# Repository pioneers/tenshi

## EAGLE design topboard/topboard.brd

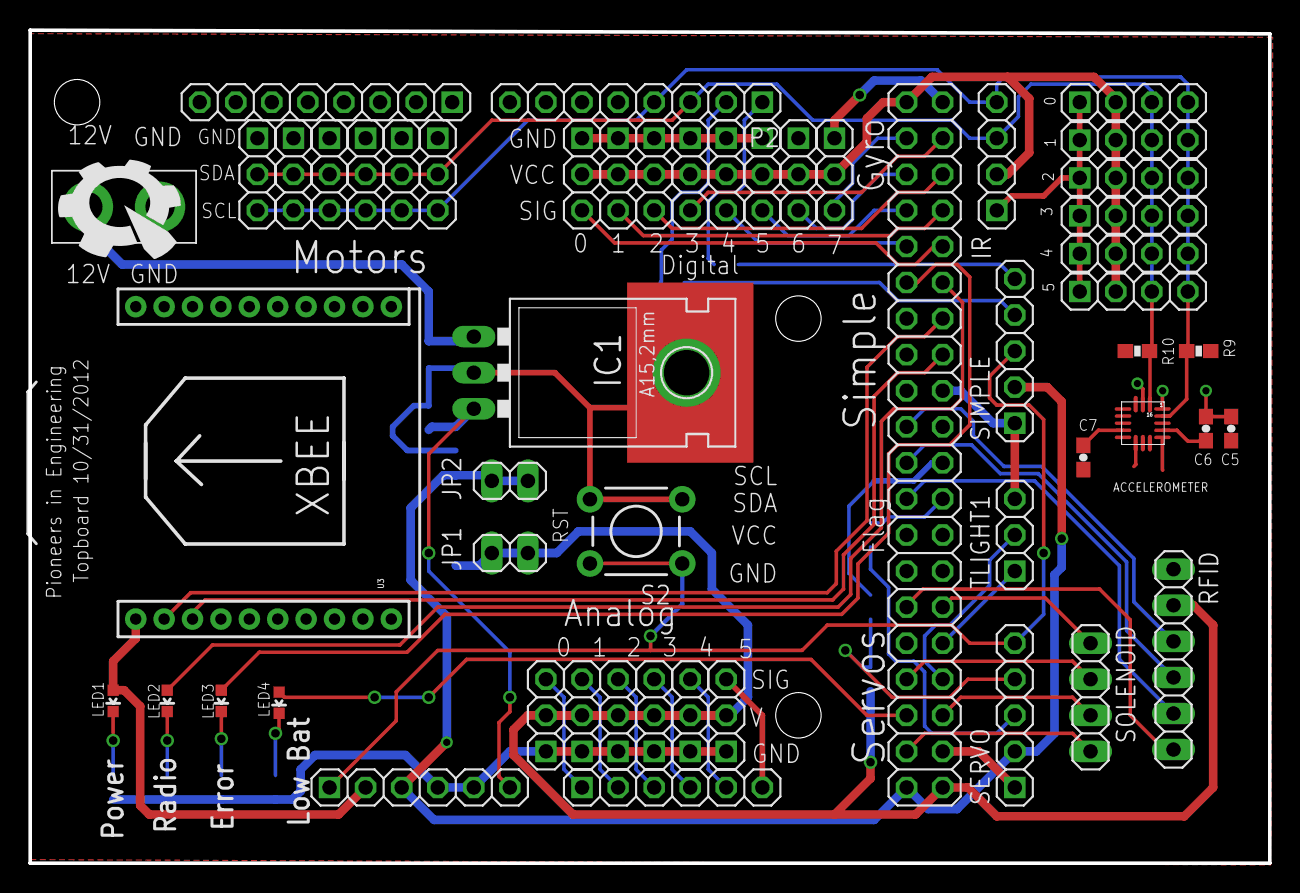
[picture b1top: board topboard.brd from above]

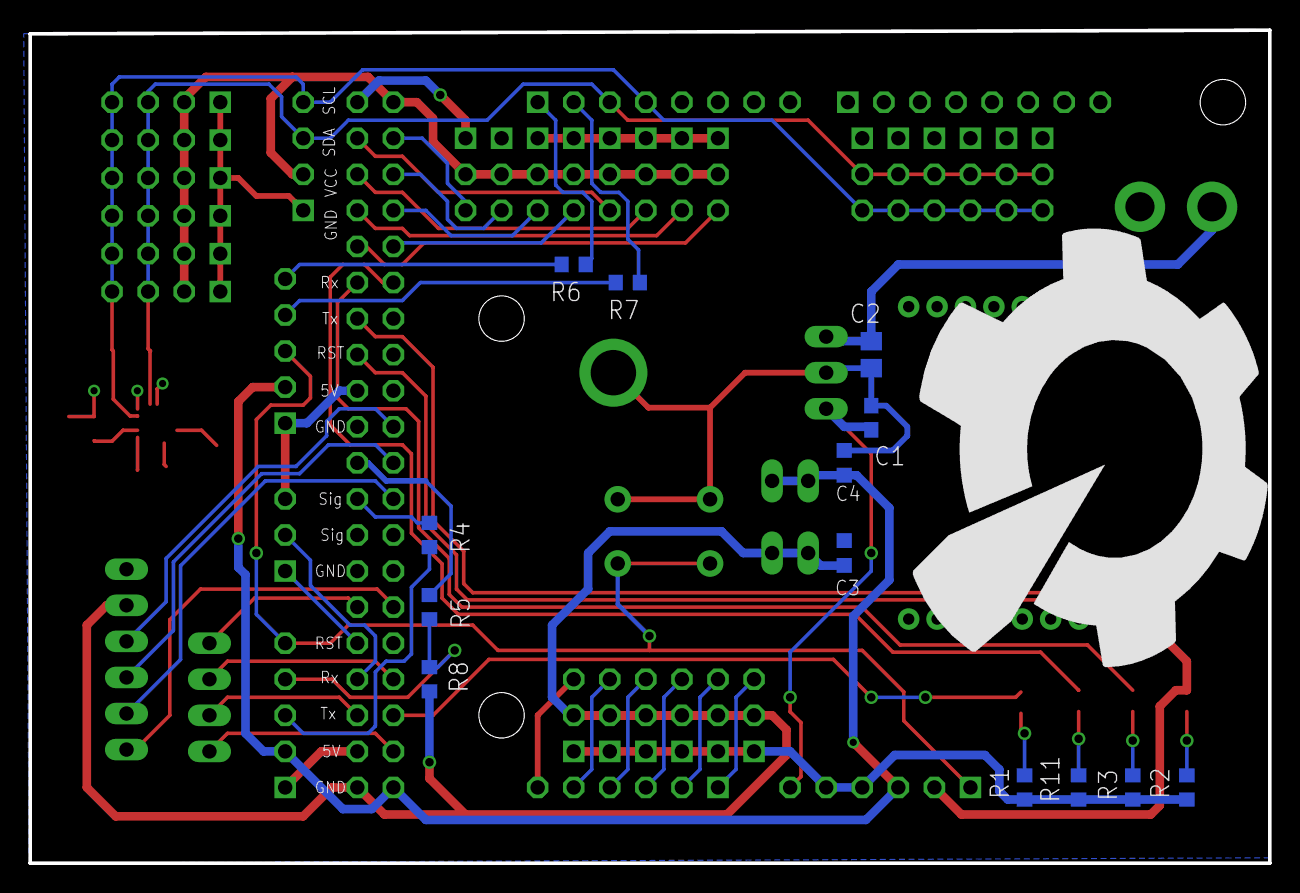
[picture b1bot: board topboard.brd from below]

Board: 2 copper layers, 87.3 x 58.7 mm, 68 parts (14 on the bottom side), 51 nets.

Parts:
0, 1, 2, 3, 4, 5: 1X04-S
A0, A1, A2, A3, A4, A5: 1X03-S
ACCELEROMETER: MMA8451QT
C1: .1uF; C0603
C2: 10uF; C0805
C3, C4: .1uF; C0603K
C5, C6: 0.1u; 0603-CAP
C7: 4.7u; 0603-CAP
D51, D52, D53, D54, D55, D56, D57, D58: 1X03-S
IC1: 78XXL
IR: 1X04-S
JP1: 3.3V; 1X02
JP2: 5v; 1X02
JP3: 1X02_XTRA_BIG
LED1, LED2, LED3, LED4: LED-0603
M1, M2, M3, M4, M5, M6: 1X03-S
P1, P2: 1X08-S
P3: 2X20
P4, P5: 1X06-S
R1, R2, R3, R7, R11: R0603
R4, R5, R6: 200; R0603
R8: 220K; R0603
R9, R10: 4.7k; 0603-RES
RFID: 1X06
S2: TACTILE-PTH
SERVO: 1X05-S
SIMPLE: Simple; 1X05-S
SOLENOID: 1X04
TLIGHT1: 1X03-S
U3: XBEE-1B2; XBEE-SILK
U$2: PIE-LOGO
U$3: PIE-LOGO-SMALL

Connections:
12V: C2.1, IC1.IN, JP3.2
+5V: C4.1, JP2.1, JP2.2, P3.39, P5.3, SERVO.2, SIMPLE.2
ADC0/IO28*: A0.3, P4.1
ADC1/IO26*: A1.3, P4.2
ADC2/IO24*: A2.3, P4.3
ADC3/AOUT/IO22*: A3.3, P4.4
ADC4/IO29: A4.3, P4.5
ADC5/IO32: A5.3, P4.6
GND: 0.1, 1.1, 2.1, 3.1, 4.1, 5.1, A0.1, A1.1, A2.1, A3.1, A4.1, A5.1, ACCELEROMETER.5, ACCELEROMETER.7, C1.2, C2.2, C3.2, C4.2, C5.2, C6.2, D51.1, D52.1, D53.1, D54.1, D55.1, D56.1, D57.1, D58.1, IC1.GND, IC1.P$1, IC1.P$2, IR.1, JP3.1, M1.1, M2.1, M3.1, M4.1, M5.1, M6.1, P1.7, P3.2, P3.18, P3.38, P5.4, P5.5, R1.1, R2.1, R3.1, R11.1, RFID.1, S2.3, S2.4, SERVO.1, SIMPLE.1, TLIGHT1.3, U3.10
IO3/RXD1: P3.22, R5.1
IO5/TXD1: P3.24, R4.1
IO6/MOSI1: P3.23, RFID.5
IO8/MISO1: P3.21, RFID.4
IO10/SCK1: P3.19, RFID.3
IO13/TXD3: P3.16, U3.3
IO17/RXD3: P3.14, U3.2
IO51: D51.3, P3.4
IO52: D52.3, P3.3
IO53: D53.3, P3.6
IO54: D54.3, P3.5
IO55: D55.3, P3.8
IO56: D56.3, P3.7
IO57: D57.3, P3.10
IO58: D58.3, P3.9
IO59: LED2.A, P3.12
IO60: LED3.A, P3.11
IO61: P3.36, SOLENOID.3
IO62: LED4.A, P3.35
IO63: P3.34, TLIGHT1.2
IO64: P3.33, SOLENOID.2
IO65: P3.32, TLIGHT1.1
IO66: P3.30, SOLENOID.1
IO67: P3.29, RFID.6
IO68: P3.37, SOLENOID.4
unnamed: LED4.C, R1.2
unnamed: LED1.C, R2.2
unnamed: LED2.C, R3.2
unnamed: R6.2, SIMPLE.5
unnamed: R4.2, SERVO.3
unnamed: R7.2, SIMPLE.4
unnamed: R5.2, R8.2, SERVO.4
unnamed: LED3.C, R11.2
unnamed: ACCELEROMETER.12, C7.2
unnamed: ACCELEROMETER.2, C6.1
RESET#: P5.1, S2.1, S2.2, SERVO.5, SIMPLE.3
RXD0/IO20*: P2.1, R6.1
SCL0/IO31*: 0.4, 1.4, 2.4, 3.4, 4.4, 5.4, ACCELEROMETER.4, IR.4, M1.3, M2.3, M3.3, M4.3, M5.3, M6.3, P2.4, R9.1
SDA0/IO33*: 0.3, 1.3, 2.3, 3.3, 4.3, 5.3, ACCELEROMETER.6, IR.3, M1.2, M2.2, M3.2, M4.2, M5.2, M6.2, P2.3, R10.1
TXD0/IO18*: P2.2, R7.1
VCC: 0.2, 1.2, 2.2, 3.2, 4.2, 5.2, A0.2, A1.2, A2.2, A3.2, A4.2, A5.2, ACCELEROMETER.1, ACCELEROMETER.14, C3.1, C5.1, C7.1, D51.2, D52.2, D53.2, D54.2, D55.2, D56.2, D57.2, D58.2, IR.2, JP1.1, JP1.2, LED1.A, P3.1, P3.40, P5.2, R8.1, R9.2, R10.2, RFID.2, U3.1
VIN: C1.1, IC1.OUT, P5.6

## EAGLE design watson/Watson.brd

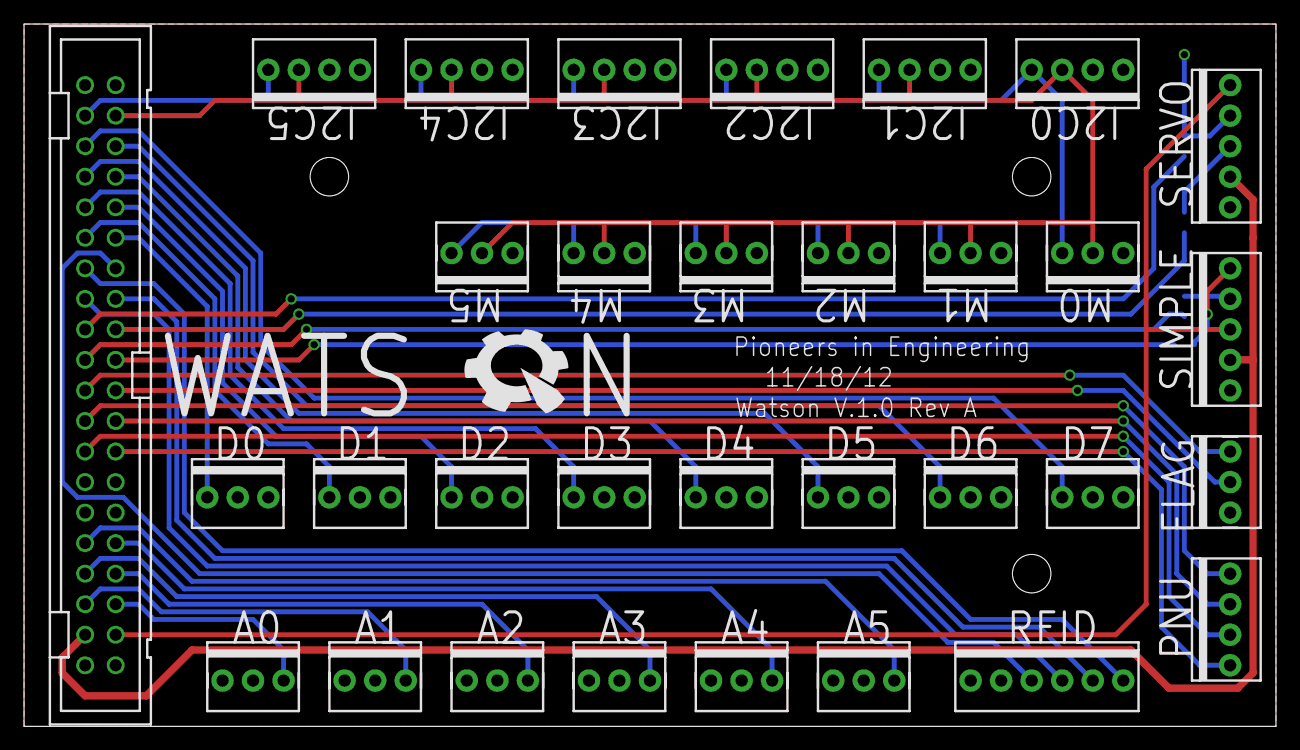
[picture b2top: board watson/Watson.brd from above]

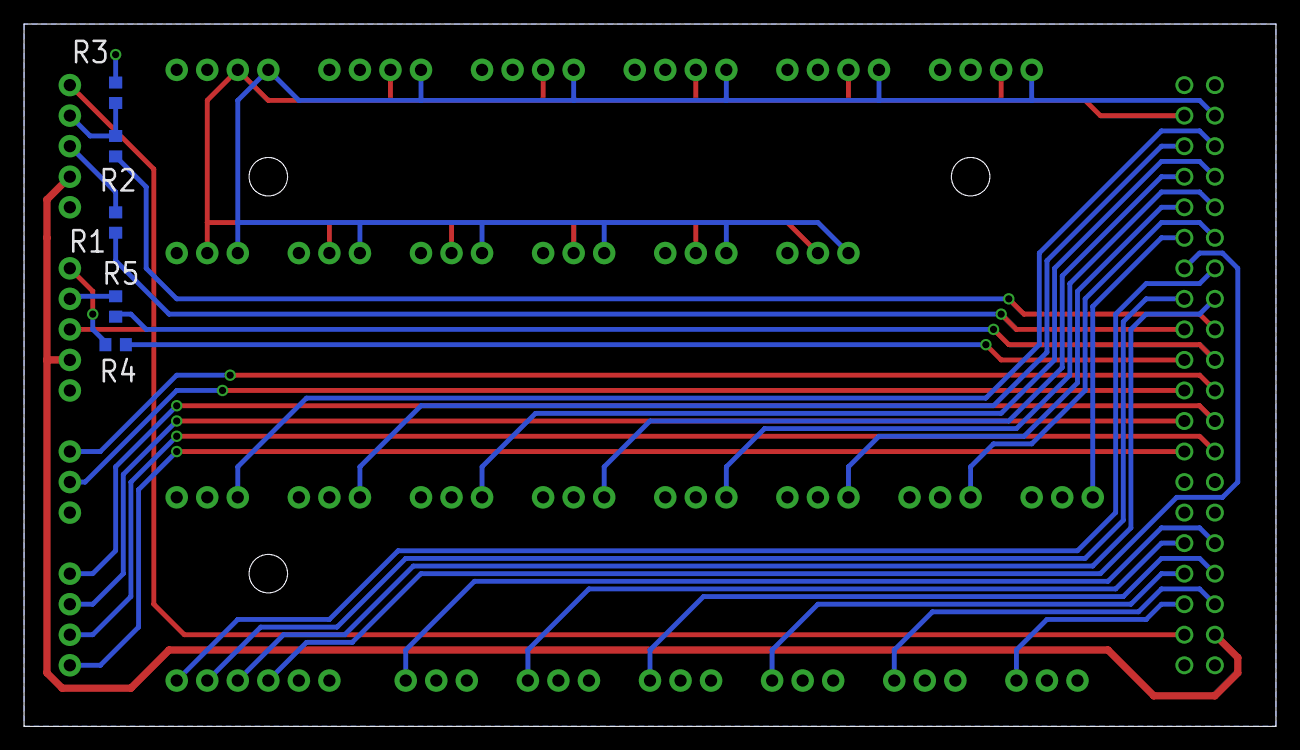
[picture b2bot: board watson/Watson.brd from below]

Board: 2 copper layers, 104.1 x 58.4 mm, 38 parts (5 on the bottom side), 38 nets.

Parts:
A0, A1, A2, A3, A4, A5: 1X03
D0, D1, D2, D3, D4, D5, D6, D7: 1X03
FLAG: 1X03
I2C0, I2C1, I2C2, I2C3, I2C4, I2C5: M04; 1X04
M0, M1, M2, M3, M4, M5: 1X03
PNU: M04; 1X04
R1, R2, R4, R5: 200; R0603
R3: 200k; R0603
RFID: M06; 1X06
SERVO: Servos; 1X05
SIMPLE: Servos; 1X05
U$1: WATSON
X1: 2540-FLAT; PAK100/2500-40

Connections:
5V: SERVO.2, SIMPLE.2, X1.4
ADC0: A5.3, X1.10
ADC1: A4.3, X1.9
ADC2: A3.3, X1.8
ADC3: A2.3, X1.7
ADC4: A1.3, X1.6
ADC5: A0.3, X1.5
GND: A0.1, A1.1, A2.1, A3.1, A4.1, A5.1, D0.3, D1.3, D2.3, D3.3, D4.3, D5.3, D6.3, D7.3, FLAG.1, I2C0.1, I2C1.1, I2C2.1, I2C3.1, I2C4.1, I2C5.1, M0.1, M1.1, M2.1, M3.1, M4.1, M5.1, RFID.1, SERVO.1, SIMPLE.1, X1.1, X1.39
IO21: PNU.3, X1.17
IO51: D7.1, X1.36
IO52: D6.1, X1.35
IO53: D5.1, X1.34
IO54: D4.1, X1.33
IO55: D3.1, X1.32
IO56: D2.1, X1.31
IO57: D1.1, X1.30
IO58: D0.1, X1.29
IO63: PNU.2, X1.16
IO64: PNU.1, X1.15
IO65: PNU.4, X1.18
IO66: FLAG.3, X1.20
IO67: FLAG.2, X1.19
IO/SELECT: RFID.6, X1.28
MISO: RFID.4, X1.26
MOSI: RFID.5, X1.25
unnamed: R2.1, R3.1, SERVO.4
unnamed: R1.1, SERVO.3
unnamed: R4.1, SIMPLE.5
unnamed: R5.1, SIMPLE.4
RESET#: SERVO.5, SIMPLE.3, X1.3
RXD1: R2.2, X1.24
RXD2: R5.2, X1.22
SCK: RFID.3, X1.27
SCL: I2C0.4, I2C1.4, I2C2.4, I2C3.4, I2C4.4, I2C5.4, M0.3, M1.3, M2.3, M3.3, M4.3, M5.3, X1.38
SDA: I2C0.3, I2C1.3, I2C2.3, I2C3.3, I2C4.3, I2C5.3, M0.2, M1.2, M2.2, M3.2, M4.2, M5.2, X1.37
TXD1: R1.2, X1.23
TXD2: R4.2, X1.21
VCC: A0.2, A1.2, A2.2, A3.2, A4.2, A5.2, D0.2, D1.2, D2.2, D3.2, D4.2, D5.2, D6.2, D7.2, I2C0.2, I2C1.2, I2C2.2, I2C3.2, I2C4.2, I2C5.2, R3.2, RFID.2, X1.2, X1.40

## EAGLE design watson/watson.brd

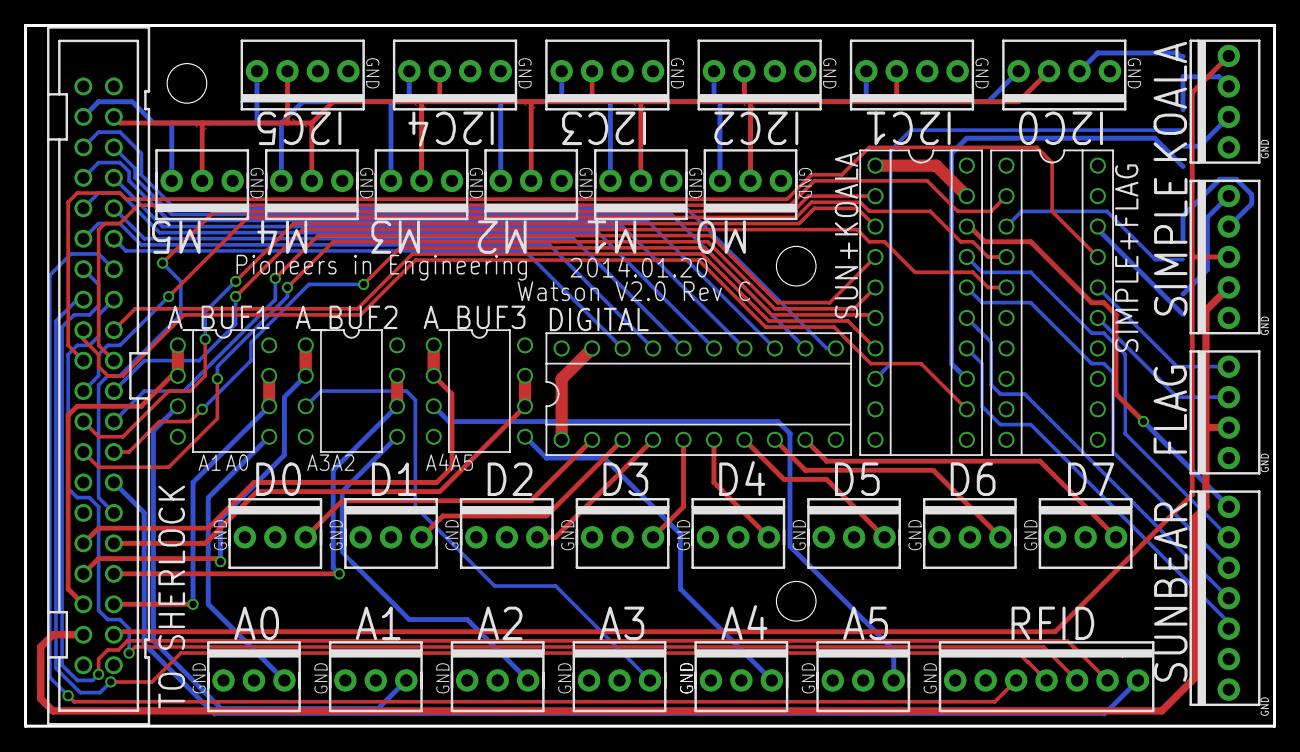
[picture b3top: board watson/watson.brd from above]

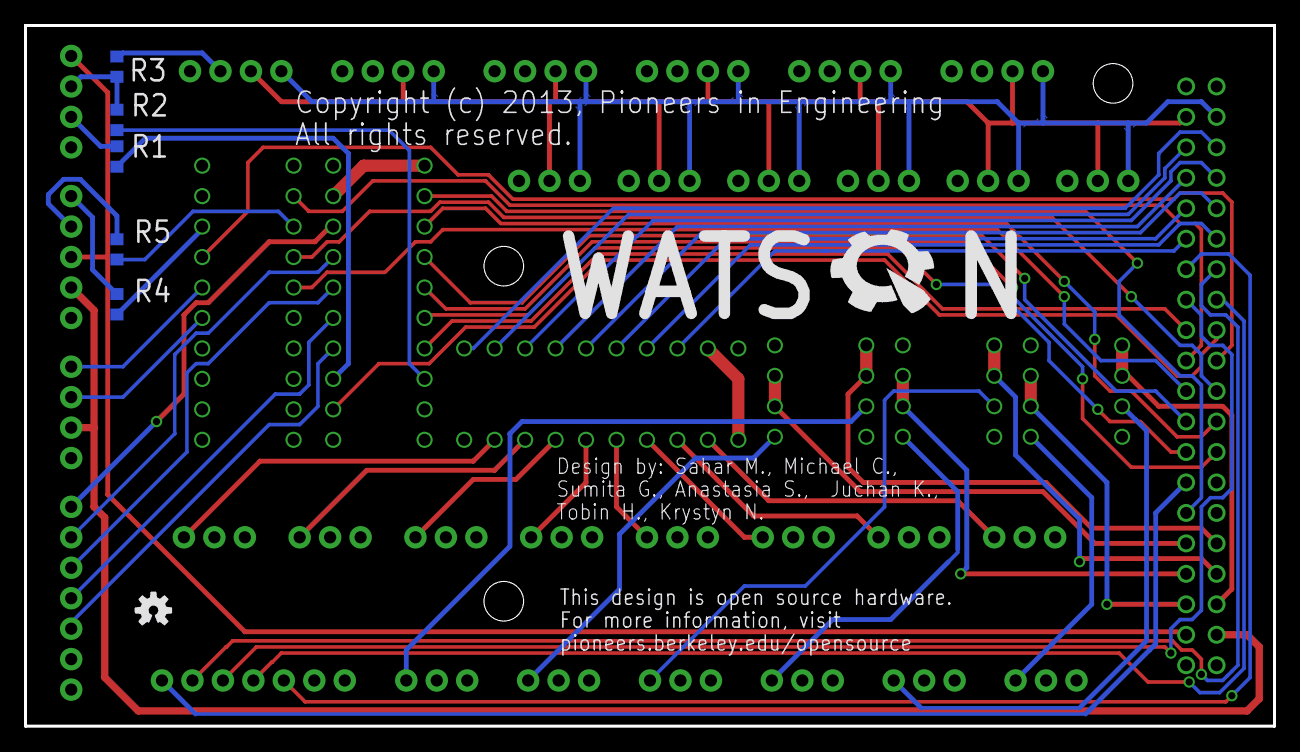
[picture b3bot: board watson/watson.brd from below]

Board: 2 copper layers, 104.1 x 58.4 mm, 48 parts (7 on the bottom side), 65 nets.

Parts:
A0, A1, A2, A3, A4, A5: 1X03-MTA
A_BUF1, A_BUF2, A_BUF3: OPAMP_DUAL_DIL
D0, D1, D2, D3, D4, D5, D6, D7: 1X03-MTA
DIGITAL: DIGITAL_BUFFER_SOCKET
FLAG: 1X04-MTA
I2C0, I2C1, I2C2, I2C3, I2C4, I2C5: 1X04-MTA
KOALA: Servos; 1X04-MTA
M0, M1, M2, M3, M4, M5: 1X03-MTA
R1, R2, R4, R5: 200; R0603
R3: 200k; R0603
RFID: M07; 1X07-MTA
SHERLOCK: 2540-; PAK100/2500-40
SIMPLE: Servos; 1X05-MTA
SIMPLE+FLAG: DIGITAL_BUFFER_SOCKET
SUN+KOALA: DIGITAL_BUFFER_SOCKET
SUNBEAR: M07; 1X07-MTA
U$1: WATSON
U$4: Mounting + Test; STAND-OFF
U$5: Test; STAND-OFF
U$6: OSHW-LOGO-S
U$7: Mounting; STAND-OFF

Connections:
+5V: FLAG.2, SHERLOCK.4, SIMPLE.2
A0: A0.3, A_BUF1.5
A1: A1.3, A_BUF1.3
A2: A2.3, A_BUF2.5
A3: A3.3, A_BUF2.3
A4: A4.3, A_BUF3.5
A5: A5.3, A_BUF3.3
ADC0/IO28*: A_BUF3.1, A_BUF3.2, SHERLOCK.10
ADC1/IO26*: A_BUF3.6, A_BUF3.7, SHERLOCK.9
ADC2/IO24*: A_BUF2.1, A_BUF2.2, SHERLOCK.8
ADC3/AOUT/IO22*: A_BUF2.6, A_BUF2.7, SHERLOCK.7
ADC4/IO29: A_BUF1.1, A_BUF1.2, SHERLOCK.6
ADC5/IO32: A_BUF1.6, A_BUF1.7, SHERLOCK.5
D0/IO58: D0.3, DIGITAL.A1
D1/IO57: D1.3, DIGITAL.A2
D2/IO56: D2.3, DIGITAL.A3
D3/IO55: D3.3, DIGITAL.A4
D4/IO54: D4.3, DIGITAL.A5
D5/IO53: D5.3, DIGITAL.A6
D6/IO52: D6.3, DIGITAL.A7
D7/IO51: D7.3, DIGITAL.A8
GND: A0.1, A1.1, A2.1, A3.1, A4.1, A5.1, A_BUF1.4, A_BUF2.4, A_BUF3.4, D0.1, D1.1, D2.1, D3.1, D4.1, D5.1, D6.1, D7.1, DIGITAL.G1, DIGITAL.G2, DIGITAL.GND, FLAG.1, I2C0.1, I2C1.1, I2C2.1, I2C3.1, I2C4.1, I2C5.1, KOALA.1, M0.1, M1.1, M2.1, M3.1, M4.1, M5.1, RFID.1, SHERLOCK.1, SHERLOCK.39, SIMPLE.1, SIMPLE+FLAG.G1, SIMPLE+FLAG.G2, SIMPLE+FLAG.GND, SUN+KOALA.G1, SUN+KOALA.G2, SUN+KOALA.GND, SUNBEAR.1
IO3/RXD1: SHERLOCK.24, SUN+KOALA.Y7
IO5/TXD1: SHERLOCK.23, SUN+KOALA.A6
IO6/MOSI1: RFID.5, SHERLOCK.25
IO8/MISO1: RFID.4, SHERLOCK.26
IO10/SCK1: RFID.3, SHERLOCK.27
IO11/RTS1: RFID.7, SHERLOCK.13
IO12: RFID.6, SHERLOCK.28
IO21: SHERLOCK.17, SUN+KOALA.A3
IO38/RXD2: SHERLOCK.22, SIMPLE+FLAG.Y2
IO39/TXD2: SHERLOCK.21, SIMPLE+FLAG.A1
IO51: DIGITAL.Y8, SHERLOCK.36
IO52: DIGITAL.Y7, SHERLOCK.35
IO53: DIGITAL.Y6, SHERLOCK.34
IO54: DIGITAL.Y5, SHERLOCK.33
IO55: DIGITAL.Y4, SHERLOCK.32
IO56: DIGITAL.Y3, SHERLOCK.31
IO57: DIGITAL.Y2, SHERLOCK.30
IO58: DIGITAL.Y1, SHERLOCK.29
IO61: SHERLOCK.11, SUN+KOALA.A1
IO63: SHERLOCK.16, SUN+KOALA.A4
IO64: SHERLOCK.15, SUN+KOALA.A5
IO65: SHERLOCK.18, SUN+KOALA.A2
IO66: SHERLOCK.20, SIMPLE+FLAG.A3
IO67: SHERLOCK.19, SIMPLE+FLAG.A4
K1/IO5/TXD1: R1.2, SUN+KOALA.Y6
K2/IO3/RXD1: R2.2, SUN+KOALA.A7
unnamed: KOALA.3, R2.1, R3.1
unnamed: KOALA.2, R1.1
unnamed: R4.1, SIMPLE.5
unnamed: R5.1, SIMPLE.4
RESET#: KOALA.4, SHERLOCK.3, SIMPLE.3
SB1/IO61: SUN+KOALA.Y1, SUNBEAR.7
SB2/IO65: SUN+KOALA.Y2, SUNBEAR.6
SB3/IO21: SUN+KOALA.Y3, SUNBEAR.5
SB4/IO63: SUN+KOALA.Y4, SUNBEAR.4
SB5/IO64: SUN+KOALA.Y5, SUNBEAR.3
SCL0/IO31*: I2C0.4, I2C1.4, I2C2.4, I2C3.4, I2C4.4, I2C5.4, M0.3, M1.3, M2.3, M3.3, M4.3, M5.3, SHERLOCK.38
SDA0/IO33*: I2C0.3, I2C1.3, I2C2.3, I2C3.3, I2C4.3, I2C5.3, M0.2, M1.2, M2.2, M3.2, M4.2, M5.2, SHERLOCK.37
SIM/IO38/RXD2: R5.2, SIMPLE+FLAG.A2
SIM/IO39/TXD2: R4.2, SIMPLE+FLAG.Y1
TF1/IO66: FLAG.4, SIMPLE+FLAG.Y3
TF2/IO67: FLAG.3, SIMPLE+FLAG.Y4
VCC: A0.2, A1.2, A2.2, A3.2, A4.2, A5.2, A_BUF1.8, A_BUF2.8, A_BUF3.8, D0.2, D1.2, D2.2, D3.2, D4.2, D5.2, D6.2, D7.2, DIGITAL.VCC, I2C0.2, I2C1.2, I2C2.2, I2C3.2, I2C4.2, I2C5.2, R3.2, RFID.2, SHERLOCK.2, SHERLOCK.40, SIMPLE+FLAG.VCC, SUN+KOALA.VCC, SUNBEAR.2

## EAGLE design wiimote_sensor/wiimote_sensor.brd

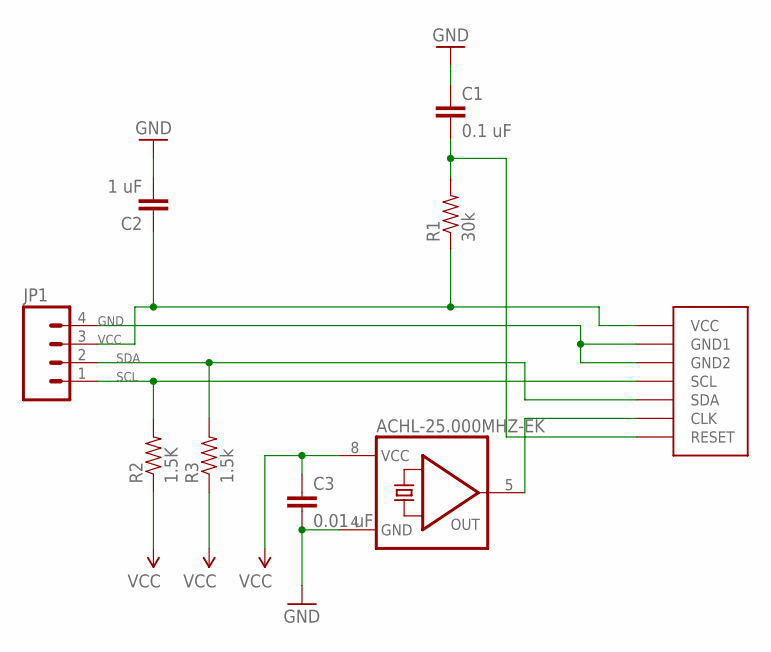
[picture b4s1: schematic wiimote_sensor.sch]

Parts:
ACHL-25.000MHZ-EK: QG5460; DIL08S
C1: 0.1 uF; 0805
C2: 1 uF; 0805
C3: 0.01 uF; 0805
JP1: M04POLAR; MOLEX-1X4
R1: 30k; 0805
R2: 1.5K; 0805
R3: 1.5k; 0805
U$1: PIXART

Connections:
CLOCK: ACHL-25.000MHZ-EK.5 (OUT), U$1.7 (CLK)
GND: ACHL-25.000MHZ-EK.4 (GND), C1.1, C2.2, C3.2, JP1.4, U$1.2 (GND1), U$1.3 (GND2)
RESET: C1.2, R1.2, U$1.8 (RESET)
SCL: JP1.1, R2.2, U$1.5 (SCL)
SDA: JP1.2, R3.2, U$1.6 (SDA)
VCC: ACHL-25.000MHZ-EK.8 (VCC), C2.1, C3.1, JP1.3, R1.1, R2.1, R3.1, U$1.1 (VCC)

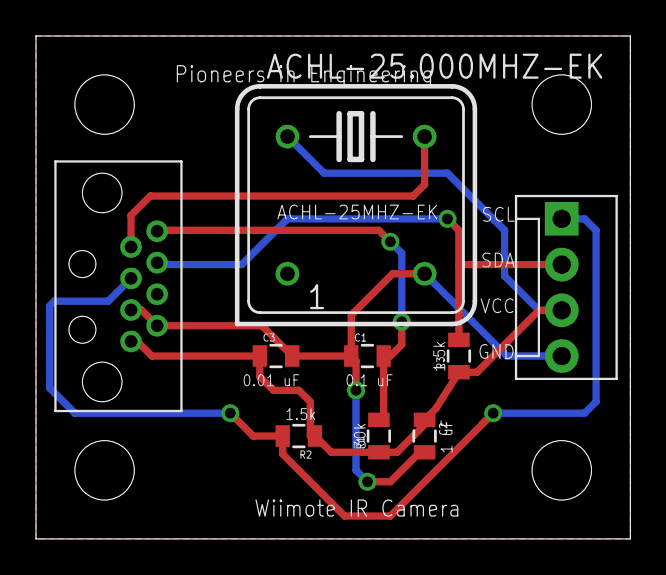
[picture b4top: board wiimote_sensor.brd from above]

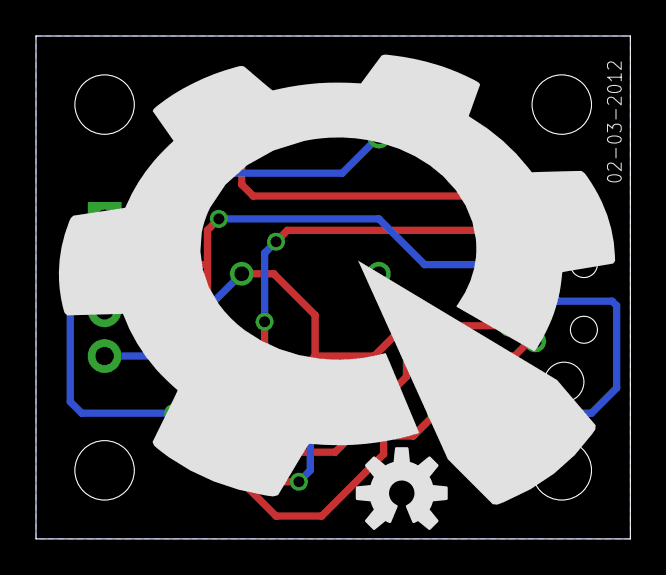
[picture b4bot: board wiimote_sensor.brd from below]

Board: 2 copper layers, 33.0 x 27.9 mm, 15 parts (2 on the bottom side), 6 nets.

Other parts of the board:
U$2: PIE-LOGO
U$3: OSHW-LOGO-M
U$4, U$5, U$6, U$7: STAND-OFF

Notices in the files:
watson/watson.brd:
Copyright (c) 2013, Pioneers in Engineering
All rights reserved.
parts and their libraries:
sparkfun: Licensing: CC v3.0 Share-Alike You are welcome to use this library for commercial purposes.
